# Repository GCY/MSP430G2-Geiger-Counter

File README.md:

# MSP430G2-Geiger-Counter

This device is Geiger-Muller Counter ,and True Random Number Generator(TRNG) uses radioactive isotopes.
</br>

## Features

- [x] Radiation Detection - CPS, CPM, uSv/h, mSv/Y
- [x] Temperature - degree Celsius (°C)
- [x] True Random Number Generator - Serial Port Output 8bit TRNG

## Hardware

### Key Component List
- Geiger-Muller Tube - J321βγ, M4011, SBM-20...etc
- MSP430G2433 or MSP430G2553
- TLC555 (CMOS 555, DIP or SMD)
- TMP35 (Operate Voltage 3.3v)
- Fuse Holder on PCB for T5x20 Size * 2

### Configure

- J1 - CMOS555 4.2v power supply.
- VR1 - Adjust High-Voltage output 180VDC~500VDC, DMM setting 1000VDC internal resistance = 10M, if you measure tube voltage around 250VDC you're doing fine(real voltage 400VDC).
- IC1 - if this is use LDO, your temperature sensor power supply voltage = 2.9v-3v(TMP35), use forward voltage(VF) 0.5v diode,  temperature sensor power supply voltage = 3.7v-4v(LM35).

</br>

### Light Sensitive Problem (J321βγ, M4011)
[Reference This Discussion](http://www.gqelectronicsllc.com/forum/topic.asp?TOPIC_ID=4540)

</br>

For J321βγ, it doesn't happen often, I guess that's about wavelength of light.

## Firmware

### Build and Burn The .hex file
- Install Energia 1.6.10E18
- Select board -> MSP430G2553
- Open MSP430Geiger.ino
- Connect Debugger BSL to MSP430Geiger
- Upload
- Done

### Key Parameters

How to calculate calibration factor? Reference [Method1,2,3,4](https://sites.google.com/site/diygeigercounter/technical/gm-tubes-supported?authuser=0 ) (SBM-20 = 175, M4011 or J321βγ = 153.8)
</br>
<pre><code>
const float CPM2uSv = 153.8f; //CPM to uSv/h conversion rate
</code></pre>

</br>
R19, R20 is 10k and 33k, LM321 gain = 1+(33k/10k) = 4.3, so original temperature voltage: temp_vol = (ADC/4.3) * (3.3/1024), every 10mV(TMP35, LM35) = 1°C, temperature = temp_vol / 0.01 °C.
<pre><code>
const float TEMPERATURE_GAIN = 1.0f + 3.3f; // 1+ (33k/10k)
const float ADC2VOL = (3.3f/1024.0f);  // 3.3v/10bit
</code></pre>

### Radiation Measurements
If detected ionizing radiation MSP430G4 P1_4 interrupt count += 1.
</br>
CPM_TIME_PERIOD 20-second sampling-rate for count-per-minute calculate, CPM = 60sec/20sec * count;
<pre><code>
const unsigned long CPM_TIME_PERIOD = 20;
</code></pre>
Next, converting CPM to a Dose Unit.
<pre><code>
uSv/h = CPM / CPM2uSv(153.8);
mSv/Y = uSv/h * 24(Day-Hour) * 365(Year-Day)
</code></pre>
The worldwide average natural dose to humans is about 2.4 mSv/Y.

### Geiger Counter TRNG Algorithm

Calculate pulse-to-pulse time period of every three counts, if (C2-C1) > (C3-C2) output current bit 0 value, (C2-C1) <= (C3-C2) output current bit 1 value, this process is physically random.

<pre><code>
/* pseudo code */
pulse_diff_time_array[3] = {C1,C2,C3};

T1 = C2-C1;
T2 = C3-C2;

if(T1 > T2){
  random_number |= (0 <<= random_number_size);
}
if(T1 <= T2){
  random_number |= (1 <<= random_number_size);
}
++random_number_size;

if(random_number_size == 8){
  Serial Output random_number;
  random_number = 0;
  random_number_size = 0;
}

</code></pre>
</br>

### Encrypt Software Demo

## Reference

- [DIYGeiger](https://sites.google.com/site/diygeigercounter)
- [Geiger Counter WiKi](https://en.wikipedia.org/wiki/Geiger_counter)
- [Hardware Random Number Generator](https://en.wikipedia.org/wiki/Hardware_random_number_generator)

LICENSE
-------

MIT License

Copyright (c) 2020 Tony Guo https://github.com/GCY

Permission is hereby granted, free of charge, to any person obtaining a copy
of this software and associated documentation files (the "Software"), to deal
in the Software without restriction, including without limitation the rights
to use, copy, modify, merge, publish, distribute, sublicense, and/or sell
copies of the Software, and to permit persons to whom the Software is
furnished to do so, subject to the following conditions:

The above copyright notice and this permission notice shall be included in all
copies or substantial portions of the Software.

THE SOFTWARE IS PROVIDED "AS IS", WITHOUT WARRANTY OF ANY KIND, EXPRESS OR
IMPLIED, INCLUDING BUT NOT LIMITED TO THE WARRANTIES OF MERCHANTABILITY,
FITNESS FOR A PARTICULAR PURPOSE AND NONINFRINGEMENT. IN NO EVENT SHALL THE
AUTHORS OR COPYRIGHT HOLDERS BE LIABLE FOR ANY CLAIM, DAMAGES OR OTHER
LIABILITY, WHETHER IN AN ACTION OF CONTRACT, TORT OR OTHERWISE, ARISING FROM,
OUT OF OR IN CONNECTION WITH THE SOFTWARE OR THE USE OR OTHER DEALINGS IN THE
SOFTWARE.

OSHW Certification
-------

https://certification.oshwa.org/tw000004.html

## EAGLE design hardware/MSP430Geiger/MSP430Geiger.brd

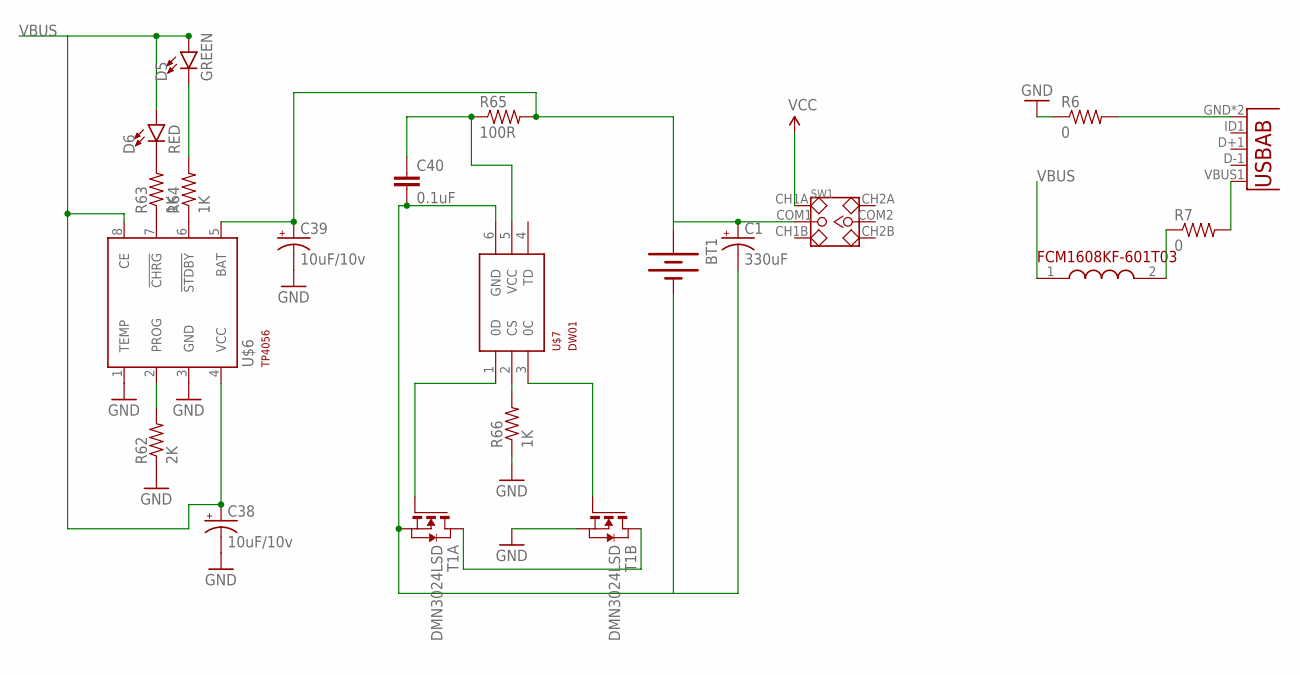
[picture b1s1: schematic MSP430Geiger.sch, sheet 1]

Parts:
BT1: BATTERYLIPO-TABS; LIPO-110-TABS
C1: 330uF; E3,5-8
C38, C39: 10uF/10v; EIA3216-KIT
C40: 0.1uF; 0603-CAP
D5: GREEN; LED-0603
D6: RED; LED-0603
R6, R7: 0; 0805
R62: 2K; 0603-RES
R63, R64, R66: 1K; 0603-RES
R65: 100R; 0603-RES
SW1: SMD-TOGGLE-SWITCH-2CH(2X3P-7X3.5MM); SW6-2.54-SMD-7.0X3.5X1.5MM
T1: DMN3024LSD; TSSOP-8
U1: USB""; USB-MICRO-SMD
U$4: FCM1608KF-601T03
U$6: TP4056; SOT23-8
U$7: DW01; SOT23-6

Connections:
GND: C38.C (-), C39.C (-), R6.1, R62.1, R66.1, T1.6 (S), T1.7 (S), U$6.1 (TEMP), U$6.3 (GND); also elsewhere on the board
unnamed: R7.2, U1.VBUS1 (VBUS)
unnamed: BT1.+, C1.+, C39.A (+), R65.2, SW1.COM1, U$6.5 (BAT)
unnamed: R7.1, U$4.2 (2.OUT)
unnamed: R6.2, U1.GND, U1.GND1 (GND)
unnamed: R62.2, U$6.2 (PROG)
unnamed: R63.1, U$6.7 (!CHRG)
unnamed: R64.1, U$6.6 (!STDBY)
unnamed: D6.C, R63.2
unnamed: D5.C, R64.2
unnamed: C40.1, R65.1, U$7.5 (VCC)
unnamed: BT1.-, C1.-, C40.2, T1.2 (S), T1.3 (S), U$7.6 (GND)
unnamed: T1.4 (G), U$7.1 (0D)
unnamed: R66.2, U$7.2 (CS)
unnamed: T1.1 (D), T1.8 (D)
unnamed: T1.5 (G), U$7.3 (0C)
VBUS: C38.A (+), D5.A, D6.A, U$4.1 (1.IN), U$6.4 (VCC), U$6.8 (CE)
VCC: SW1.CH1A; also elsewhere on the board

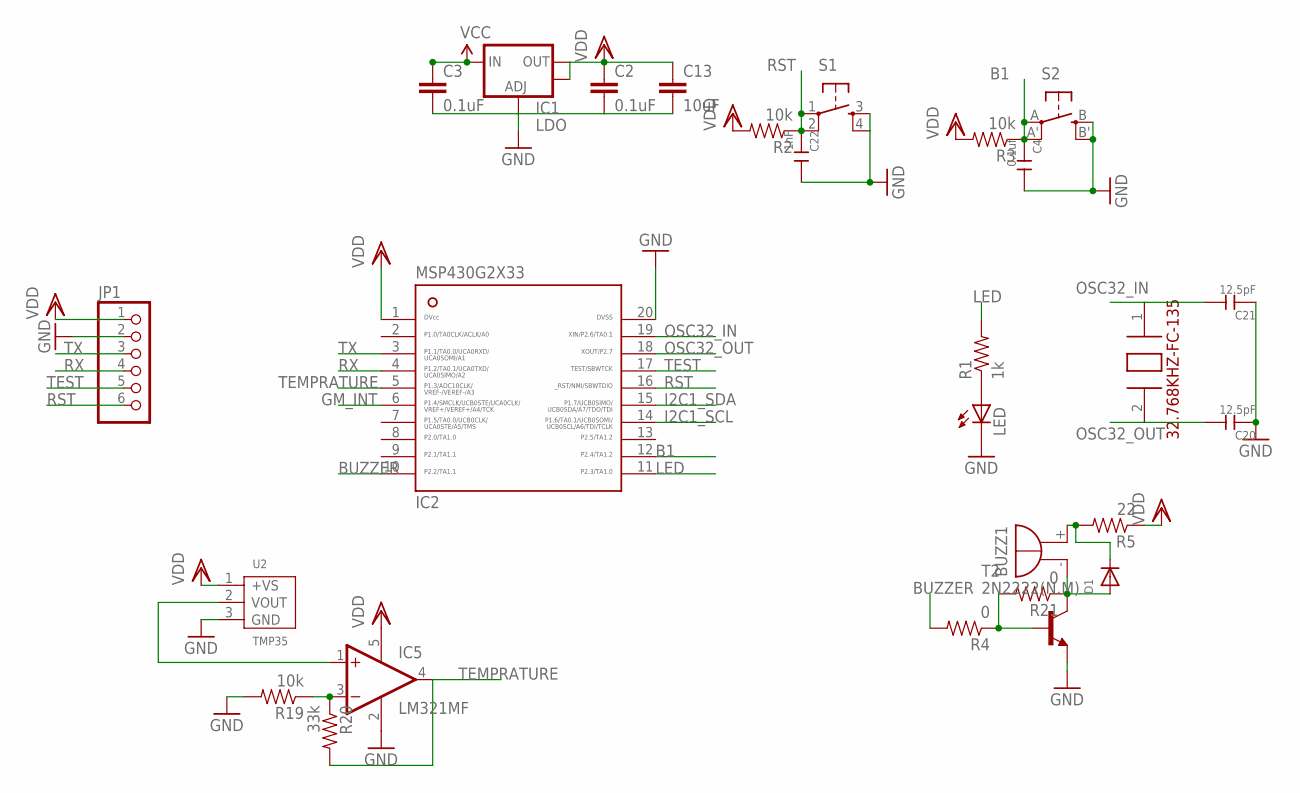
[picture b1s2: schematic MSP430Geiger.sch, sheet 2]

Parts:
BUZZ1: F/QMBIII
C2, C3: 0.1uF; 0603-CAP
C4: 0.1uf; C0603
C13: 10uF; 0603-CAP
C20, C21: 12.5pF; C0603
C22: 1nF; C0603
D1: DIODESMA; SMADIODE
IC1: LDO; SOT223
IC2: MSP430; PW20
IC5: LM321MF; SOT23-5
JP1: PINHD-1X6; 1X06
LED: LEDCHIP-LED0805; CHIP-LED0805
R1: 1k; 0805
R2, R3: 10k; 0603
R4, R21: 0; 0805
R5: 22; 0805
R19: 10k; 0805
R20: 33k; 0805
S1: TAC_SWITCHSMD; TACTILE_SWITCH_SMD
S2: SPST_TACT-EVQQ2; EVQ-Q2
T2: 2N2222(N.M); SOT23-EBC
U2: TMP35; TO-92-3
U$8: 32.768KHZ-FC-135

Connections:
B1: C4.1, IC2.12, R3.1, S2.A, S2.A' (P1)
BUZZER: IC2.10, R4.2
GM_INT: IC2.6; also elsewhere on the board
GND: C2.2, C3.2, C4.2, C13.2, C20.1, C21.1, C22.2, IC1.1 (ADJ), IC2.20, IC5.2 (V-), JP1.2, LED.C, R19.2, S1.3, S1.4, S2.B (S), S2.B' (S1), T2.E, U2.3 (GND); also elsewhere on the board
I2C1_SCL: IC2.14; also elsewhere on the board
I2C1_SDA: IC2.15; also elsewhere on the board
LED: IC2.11, R1.2
unnamed: R4.1, R21.2, T2.B
unnamed: LED.A, R1.1
unnamed: BUZZ1.- (+), D1.A, R21.1, T2.C
unnamed: BUZZ1.+ (-), D1.C, R5.2
unnamed: IC5.3 (-IN), R19.1, R20.1
unnamed: IC5.1 (+IN), U2.2 (VOUT)
OSC32_IN: C21.2, IC2.19, U$8.1 (1.XIN)
OSC32_OUT: C20.2, IC2.18, U$8.2 (2.XIN)
RST: C22.1, IC2.16, JP1.6, R2.1, S1.1, S1.2
RX: IC2.4, JP1.4
TEMPRATURE: IC2.5, IC5.4 (OUT), R20.2
TEST: IC2.17, JP1.5
TX: IC2.3, JP1.3
VCC: C3.1, IC1.3 (IN); also elsewhere on the board
VDD: C2.1, C13.1, IC1.2 (OUT), IC1.4 (OUT), IC2.1, IC5.5 (V+), JP1.1, R2.2, R3.2, R5.1, U2.1 (+VS); also elsewhere on the board

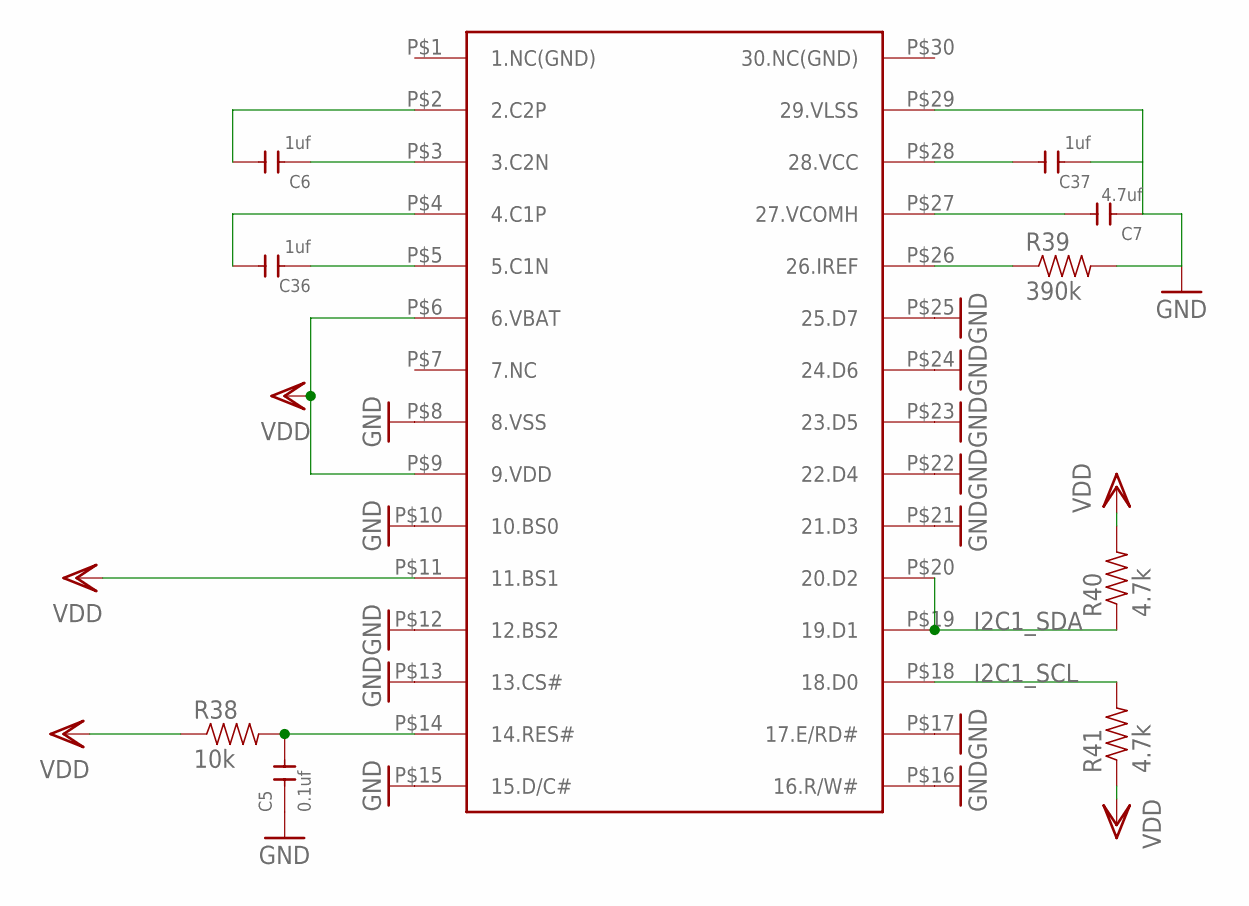
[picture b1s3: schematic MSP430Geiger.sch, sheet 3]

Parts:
C5: 0.1uf; C0603
C6, C36, C37: 1uf; C0603
C7: 4.7uf; C0603
R38: 10k; 0603
R39: 390k; 0603
R40, R41: 4.7k; 0603
U$18: ER-OLED0.96

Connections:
GND: C5.1, C7.1, C37.1, R39.2, U$18.P$8 (8.VSS), U$18.P$10 (10.BS0), U$18.P$12 (12.BS2), U$18.P$13 (13.CS#), U$18.P$15 (15.D/C#), U$18.P$16 (16.R/W#), U$18.P$17 (17.E/RD#), U$18.P$21 (21.D3), U$18.P$22 (22.D4), U$18.P$23 (23.D5), U$18.P$24 (24.D6), U$18.P$25 (25.D7), U$18.P$29 (29.VLSS); also elsewhere on the board
I2C1_SCL: R41.2, U$18.P$18 (18.D0); also elsewhere on the board
I2C1_SDA: R40.1, U$18.P$19 (19.D1), U$18.P$20 (20.D2); also elsewhere on the board
unnamed: C5.2, R38.2, U$18.P$14 (14.RES#)
unnamed: C6.1, U$18.P$3 (3.C2N)
unnamed: C36.1, U$18.P$5 (5.C1N)
unnamed: C6.2, U$18.P$2 (2.C2P)
unnamed: C36.2, U$18.P$4 (4.C1P)
unnamed: R39.1, U$18.P$26 (26.IREF)
unnamed: C7.2, U$18.P$27 (27.VCOMH)
unnamed: C37.2, U$18.P$28 (28.VCC)
VDD: R38.1, R40.2, R41.1, U$18.P$6 (6.VBAT), U$18.P$9 (9.VDD), U$18.P$11 (11.BS1); also elsewhere on the board

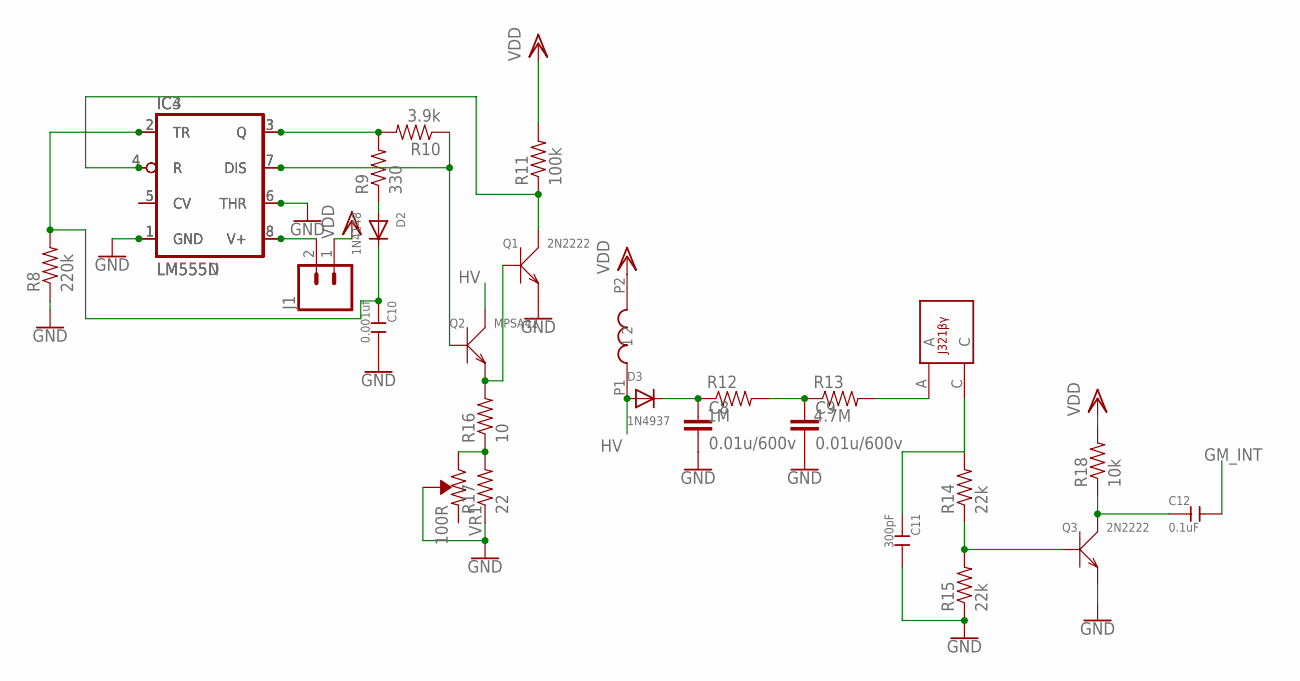
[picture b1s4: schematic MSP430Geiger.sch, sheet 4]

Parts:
C8, C9: 0.01u/600v; C15B5
C10: 0.001uf; C0603
C11: 300pF; C0603
C12: 0.1uF; C0603
D2: 1N4148; SMADIODE
D3: 1N4937; SMADIODE
IC3: LM555D; SO08
IC4: LM555N; DIL08-ROUND
J1: CONN_02; 1X02
Q1, Q3: 2N2222; SOT-23
Q2: MPSA42; SOT-23
R8: 220k; 0603
R9: 330; 0603
R10: 3.9k; 0603
R11: 100k; 0603
R12: 1M; 0603
R13: 4.7M; 0603
R14, R15: 22k; 0603
R16: 10; 0603
R17: 22; 0603
R18: 10k; 0603
U$1: J321βγ
U$2: 10mF; CD54
VR1: 100R; TRIMPOT-SMD-3MM-CLOSED

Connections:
GM_INT: C12.2; also elsewhere on the board
GND: C8.2, C9.2, C10.2, C11.2, IC3.1 (GND), IC3.6 (THR), IC4.1 (GND), IC4.6 (THR), Q1.2 (E), Q3.2 (E), R8.1, R15.1, R17.1, VR1.2 (WIPER); also elsewhere on the board
HV: D3.A, Q2.3 (C), U$2.P1 (1)
unnamed: IC3.3 (Q), IC4.3 (Q), R9.2, R10.2
unnamed: D2.A, R9.1
unnamed: IC3.7 (DIS), IC4.7 (DIS), Q2.1 (B), R10.1
unnamed: C10.1, D2.C, IC3.2 (TR), IC4.2 (TR), R8.2
unnamed: IC3.4 (R), IC4.4 (R), Q1.3 (C), R11.1
unnamed: Q1.1 (B), Q2.2 (E), R16.2
unnamed: C8.1, D3.C, R12.1
unnamed: C9.1, R12.2, R13.1
unnamed: R16.1, R17.2, VR1.3 (CW)
unnamed: IC3.5 (CV), IC4.5 (CV)
unnamed: R13.2, U$1.A
unnamed: C11.1, R14.2, U$1.C
unnamed: Q3.1 (B), R14.1, R15.2
unnamed: IC3.8 (V+), IC4.8 (V+), J1.2
unnamed: C12.1, Q3.3 (C), R18.1
VDD: J1.1, R11.2, R18.2, U$2.P2 (2); also elsewhere on the board

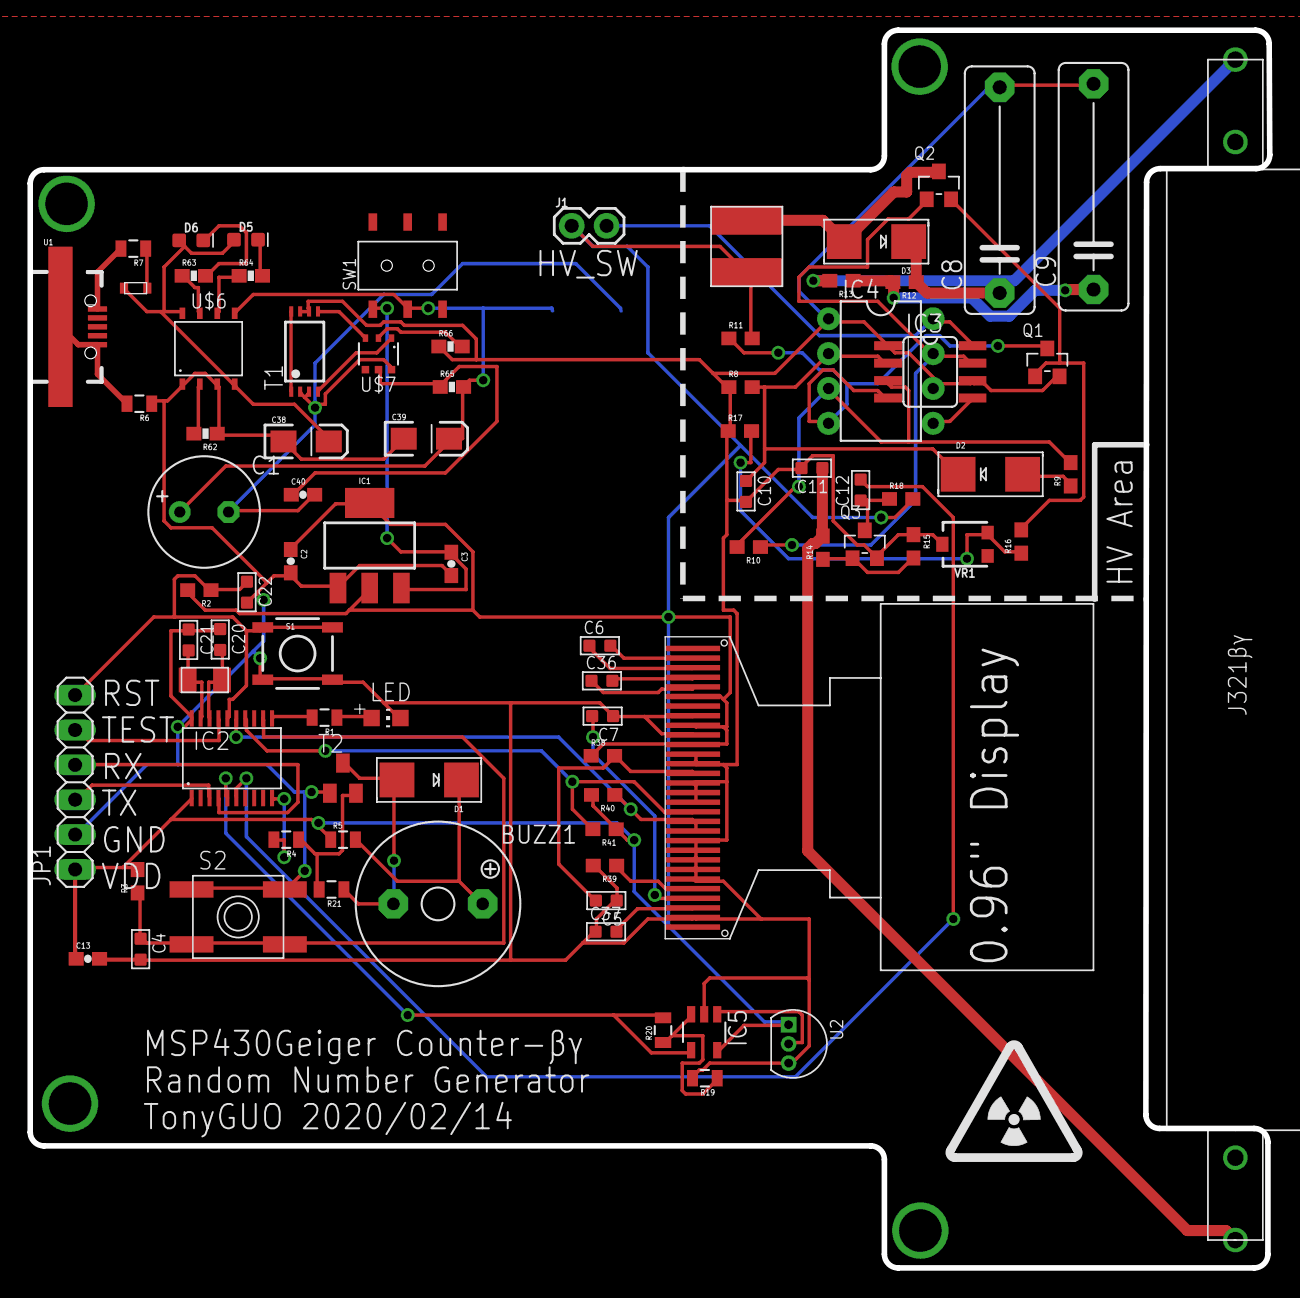
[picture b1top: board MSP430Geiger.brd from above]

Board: 2 copper layers, 90.3 x 90.2 mm, 85 parts (1 on the bottom side), 62 nets.

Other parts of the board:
U$3: RADIOACTIVE_10.00

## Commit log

2020-03-27 Eagle PCB V1.1
2020-03-27 picture
2020-04-06 ver 1.0
2020-04-06 TRNG mode
2020-04-06 TRGN File
2020-04-07 calibration factor
2020-04-07 histogram
2020-04-07 serial output random number
2020-04-08 edit
2020-06-11 add dead zone
2021-10-14 add OSHWA certification

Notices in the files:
parts and their libraries:
SparkFun-Capacitors: Licensing: CC v3.0 Share-Alike You are welcome to use this library for commercial purposes.
SparkFun-Retired: Licensing: Creative Commons ShareAlike 4.0 International - https://creativecommons.org/licenses/by-sa/4.0
